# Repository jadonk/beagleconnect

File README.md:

# BeagleConnect
The purpose of BeagleConnect is to eliminate the need to write software to connect to a massive library of [sensors](https://en.wikipedia.org/wiki/Sensor), [actuators](https://en.wikipedia.org/wiki/Actuator) and [indicators](https://en.wikipedia.org/wiki/Indicator_(distance_amplifying_instrument)). These are the tools used to automate things in [mechatronics](https://en.wikipedia.org/wiki/Mechatronics) and [IoT](https://en.wikipedia.org/wiki/Internet_of_things).

BeagleConnect solves:
* The need to write software to add a large set of diverse devices to your system,
* The need to maintain the software with security updates,
* The need to rapidly prototype using off-the-shelf software and hardware without wiring,
* The need to connect to devices using long-range, low-power wireless, and
* The need to produce high-volume custom hardware cost-optimized for your requirements.

The minimally viable BeagleConnect development release:
* Supports at least 100 mikroBUS-based Click boards from Mikroelectronika,
* Works with BLE-enabled Linux computers at 2.4GHz,
* Works on long-range sub-GHz at 500m with data rates of 1kbps, and
* Comprises of low-cost BeagleBoard.org Linux SBC, a BeagleConnect gateway, and at least 10 BeagleConnect device nodes each supporting 2 add-on devices.

A wireless BeagleConnect board for adding a new device node is targeted to cost under US$10.

Future releases will be collaborated with the community, evolve dynamically, and contain additional functionality. The goal is to support over 500 add-on devices within the first year after the development release.

_Aside_: The term BeagleConnect refers to a particular board as well as a family of boards, a collection of Linux kernel drivers, microcontroller firmware, communication protocol, and system-level integration to automation software tools. More specific terms will be applied in the architecture details. The term is meant to represent the experience to be introduced to users through the initial BeagleConnect board.

## BeagleConnect wireless board prototype rev B

# What is new?
BeagleConnect solves IoT in a different and better way than any previous solution.

## The device interface software is already done
BeagleConnect uses the collaboratively developed Linux kernel to contain the intelligence required to speak to these devices (sensors, actuators, and indicators), rather than relying on writing code on a microcontroller specific to these devices. Some existing solutions rely on large libraries of microcontroller code, but the integration of communications, maintenance of the library with a limited set of developer resources and other constraints to be explained later make those other solutions less suitable for rapid prototyping than BeagleConnect.

Linux presents these devices abstractly in ways that are self-descriptive. Add an accelerometer to the system and you are automatically fed a stream of force values in standard units. Add a temperature sensor and you get it back in standard units again. Same for sensing magnetism, proximity, color, light, frequency, orientation, or multitudes of other inputs. Indicators, such as LEDs and displays, are similarly abstracted with a few other kernel subsystems and more advanced actuators with and without feedback control are in the process of being developed and standardized. In places where proper Linux kernel drivers exist, no new specialized code needs to be created for the devices.

*Bottom line*: For hundreds of devices, users won't have to write a single line of code to add them their systems. The automation code they do write can be extremely simple, done with graphical tools or in any language they want. Maintenance of the code is centralized in a small reusable set of microcontroller firmware and the Linux kernel, which is highly peer reviewed under a [highly-regarded governance model](https://wiki.p2pfoundation.net/Linux_-_Governance).

## On-going maintenance
Because there isn't code specific to any given network-of-devices configuration, we can all leverage the same software code base. This means that when someone fixes an issue in either BeagleConnect firmware or the Linux kernel, you benefit from the fixes. The source for BeagleConnect firmware is also submitted to the [Zephyr Project](https://www.zephyrproject.org/) upstream, further increasing the user base. Additionally, we will maintain stable branches of the software and provide mechanisms for updating firmware on BeagleConnect hardware. With a single, relatively small firmware load, the potential for bugs is kept low. With large user base, the potential for discovering and resolving bugs is high.

## Rapid prototyping without wiring
BeagleConnect utilizes the [mikroBUS standard](https://elinux.org/Mikrobus). The mikroBUS standard interface is flexible enough for almost any typical sensor or indicator with hundreds of devices available.

## Long-range, low-power wireless
BeagleConnect wireless hardware is built around a [TI CC1352](http://www.ti.com/product/CC1352R) with TODO benefits.

## Full customization possible
BeagleConnect utilizes [open source hardware](https://www.oshwa.org/definition/) and [open source software](https://en.wikipedia.org/wiki/Open-source_software), making it possible to optimize hardware and software implementations and sourcing to meet end-product requirements. BeagleConnect is meant to enable rapid-prototyping and not to necessarily satisfy any particular end-product's requirements, but with full considerations for go-to-market needs.

BeagleConnect is:
* Available for at least 10 years,
* Built with fully open source software with submissions to mainline Linux and Zephyr repositories to aide in support and porting,
* Built with fully open source and non-restrictive hardware design including schematic, bill-of-materials, layout, and manufacturing files (with only the BeagleBoard.org logo removed due to licensing restrictions of our brand),
* Built with parts where at least a compatible part is available from worldwide distributors in any quantity,
* Built with design and manufacturing partners able to help scale derivative designs,
* Based on a security model using public/private keypairs that can be replaced to secure your own network, and
* Fully FCC/CE certified.

# Usage and development

## BeagleConnect user experience

### Enable a Linux host with BeagleConnect

Log into a host system running Linux that is BeagleConnect enabled. Enable a Linux host with BeagleConnect by plugging a BeagleConnect board into it's USB port. You'll also want to have another BeagleConnect board with a sensor, actuator or indicator device on it.

TODO: Currently the host is shown to be a PocketBeagle with a cape, but should likely be a different SBC with a BeagleConnect board connected over USB.

TODO: Currently the device is shown to be a Sensortag, but should likely be shown as a BeagleConnect with a Click Board device on it and a battery.

### Connect host and device

Initiate a connection between the host and devices by pressing the discovery button(s).

### Device data shows up as files

New streams of self-describing data show up on the host system using native device drivers.

## Components
* Host-side: BeagleConnect board connects a CC1352 to a Beagle or other Linux host over USB to serial
   * Provides long-range, low-power wireless communications
* Device-side: BeagleConnect board with a CC1352 is powered by a battery (coin cell or JST connector) or USB connector
   * Provides 2 mikroBUS connectors for connecting any of hundreds of [Click Board](https://bbb.io/click) mikroBUS add-on devices
* Standard firmware on the host-side and target-side CC1352s transport the standard busses
   * Paired with a Linux kernel driver
   * Provides new Linux host controllers for SPI, I2C, UART, PWM, ADC, and GPIO with interrupts
* Two-step provisioning
   * Enter provisioning mode by pressing the button on the host-side BeagleConnect
   * Press the button on any powered device-side BeagleConnect to add it to the network
      * The device interfaces get exposed to the host via Greybus BRIDGED_PHY protocol
      * The I2C bus is probed for a an identifier EEPROM and appropriate device drivers are loaded on the host
      * Unsupported Click Boards connected are exposed via userspace drivers on the host for development

### What's different
* No microcontroller code development is required by users
* Userspace drivers make rapid prototyping really easy
* Kernel drivers makes the support code collaborative parts of the Linux kernel, rather than cut-and-paste

## Development platform
* Linux machine
* 2x [CC1352R Launchpad](http://www.ti.com/tool/launchxl-cc1352r1)
* [Click BoosterPack 2](https://www.mikroe.com/click-booster-pack-2)

# Technical approach

BeagleConnect uses Greybus and updated Click Boards with identifiers to eliminate the need to add manually configure devices added onto the Linux system.

## High-level
* For Linux nerds: Think of BeagleConnect as [6LoWPAN](https://en.wikipedia.org/wiki/6LoWPAN) over [802.15.4](https://en.wikipedia.org/wiki/IEEE_802.15.4)-based [Greybus](https://kernel-recipes.org/en/2015/talks/an-introduction-to-greybus/) (instead of Unipro as used by Project Ara), where every BeagleConnect board shows up as new SPI, I2C, UART, PWM, ADC, and GPIO controllers that can now be probed to load drivers for the sensors or whatever is connected to them. (Proof of concept of Greybus over TCP/IP: https://www.youtube.com/watch?v=7H50pv-4YXw)
* For MCU folks: Think of BeagleConnect as a [Firmata](https://github.com/firmata/protocol)-style firmware load that exposes the interfaces for remote access over a secured wireless network. However, instead of using host software that knows how to speak the Firmata protocol, the Linux kernel speaks the slightly similar Greybus protocol to the MCU and exposes the device generically to users using a Linux kernel driver. Further, the Greybus protocol is spoken over [6LoWPAN](https://en.wikipedia.org/wiki/6LoWPAN) on [802.15.4](https://en.wikipedia.org/wiki/IEEE_802.15.4).

## Software architecture
* 802.15.4 provides the 

## TODO items
* Linux kernel driver
* Provisioning
   * Kconfig and what-not for adding a new BeagleDust to the network
   * Kconfig and what-not for configuring Clicks connected to BeagleDust
* Firmware for host CC13x
* Firmware for device CC13x
* Click Board drivers and device tree formatted metadata for 100 or so Click Boards
* Click Board plug-ins for node-red for the same 100 or so Click Boards
* BeagleDust System Reference Manual and FAQs

## Associated pre-work
* Click Board support for Node-RED can be executed with native connections on PocketBeagle+TechLab and BeagleBone Black with mikroBUS Cape
   * Device tree fragments and driver updates can be provided via https://bbb.io/click
* The Kconfig style provisioning can be implemented for those solutions, which will require a reboot. We need to centralize edits to /boot/uEnv.txt to be programmatic. As I think through this, I don't think BeagleConnect is impacted, because the Greybus-style discovery along with Click EEPROMS will eliminate any need to edit /boot/uEnv.txt.

## User experience concerns
* Make sure no reboots are required
* Plugging BeagleConnect into host should trigger host configuration
* Click EEPROMs should trigger loading whatever drivers are needed and provisioning should load any new drivers
* Userspace (spidev, etc.) drivers should unload cleanly when 2nd phase provisioning is completed

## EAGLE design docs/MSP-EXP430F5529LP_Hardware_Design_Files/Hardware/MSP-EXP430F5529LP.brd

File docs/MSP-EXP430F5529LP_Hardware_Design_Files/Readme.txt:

MSP-EXP430F5529LP Hardware Design Files v1.05.00
Texas Instruments, Inc.

********************************************************************************
Welcome to the MSP-EXP430F5529LP LaunchPad!
********************************************************************************

In this package, you will find hardware design files that can help you quickly
get started on developing your own project.

Available in the 'Hardware' folder are the complete board schematic and layout,
bill of material and Gerber files.

You can also find various web links in the 'Documentation' folder pointing to
the Tool Page, Quick Start Guide, User's Guide and MSP430 USB Developers Package.

For more resources, be sure to visit http://www.ti.com/tool/MSP-EXP430F5529LP
Also checkout the Wiki page at http://processors.wiki.ti.com/index.php/MSP430F5529_LaunchPad

********************************************************************************
Revision History
********************************************************************************
Ver 1.05.00 - June 22nd, 2015
- Added MacOSX + Linux support for MSP430Flasher

Ver 1.04.00 - March 24th, 2015
- Updated driverlib and USB stack in software examples

Ver 1.03.00 - September 26th, 2014
- Updated Hardware files to Revision 1.6

Ver 1.02.00 - June 23rd, 2014
- Updated release packages to distribute hardware and software files separately

Ver 1.01.00 - Jan 2nd, 2014
- Updated Hardware files to Revision 1.5

Ver 1.00.01 - October 09th, 2013
- Added Code Size limited project for emulStorageKeyboard
- Added new folder to include emulation tool driver and simpleUsbBackChannel driver

Ver 1.00.00 - August 27th, 2013
- Initial Release

********************************************************************************
Project File Listing
********************************************************************************
|--Documentation              : Folder containing links to more resources
|--Hardware                   : Folder containing board design files, bill of
                                material and gerber files
|--Readme.txt                 : This file

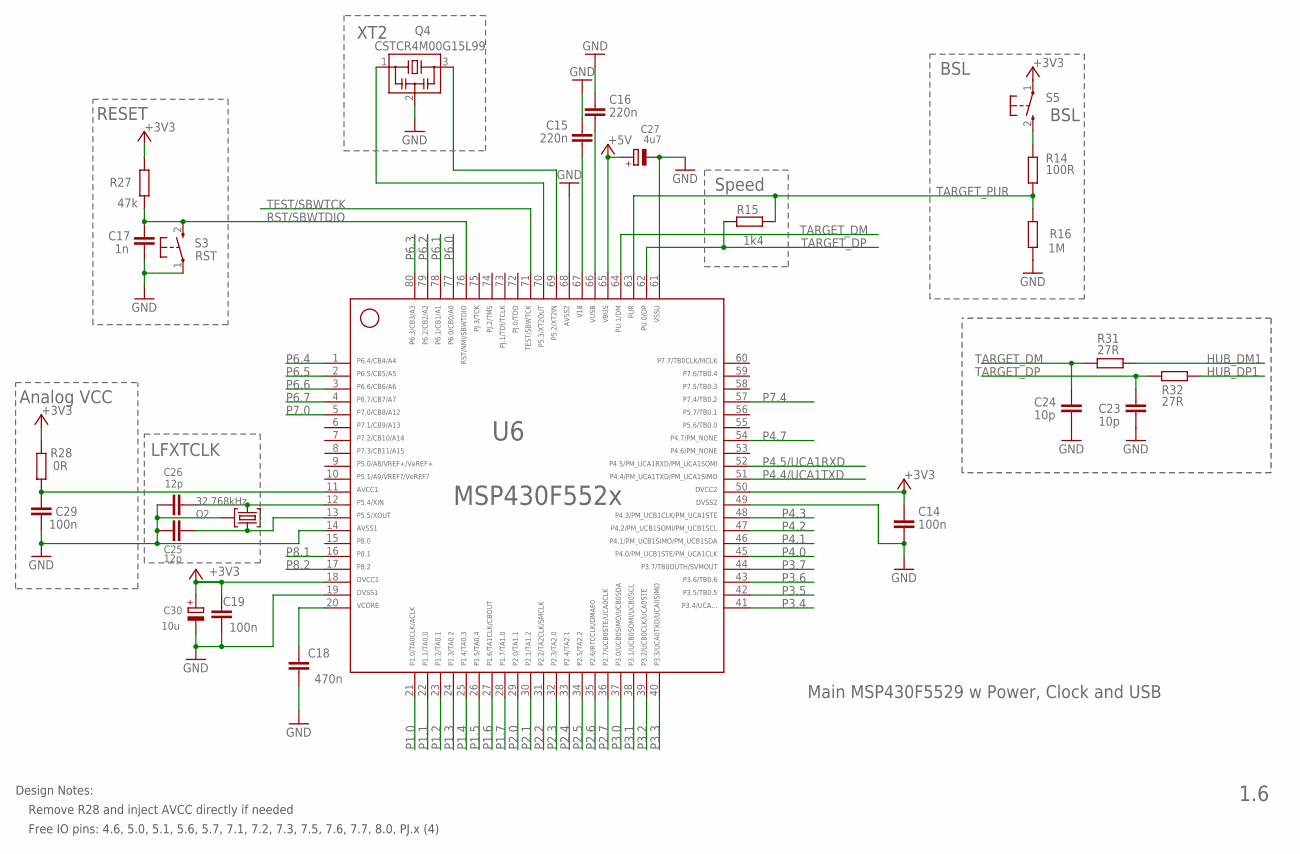
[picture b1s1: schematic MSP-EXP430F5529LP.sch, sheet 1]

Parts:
C14, C19, C29: 100n; 0402
C15, C16: 220n; 0402
C17: 1n; 0402
C18: 470n; 0402
C23, C24: 10p; 0402
C25, C26: 12p; 0402
C27: 4u7; A/3216-18R
C30: 10u; A/3216-18R
Q2: 32.768kHz; MS3V-T1R
Q4: CSTCR4M00G15L99; MURATA-FILTER_CSTCR
R14: 100R; 0402
R15: 1k4; 0402
R16: 1M; 0402
R27: 47k; 0402
R28: 0R; 0402
R31, R32: 27R; 0402
S3: RST; PBTH
S5: BSL; PBTH
U6: MSP430F5529IPNR; PN80

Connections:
+3V3: C14.1, C19.2, C30.+, R27.2, R28.2, S5.1, U6.18, U6.50; also elsewhere on the board
+5V: C27.+, U6.65; also elsewhere on the board
AVCC: C29.1, R28.1, U6.11
GND: C14.2, C15.2, C16.2, C17.2, C18.1, C19.1, C23.2, C24.2, C25.1, C26.1, C27.-, C29.2, C30.-, Q2.P3 (GND), Q4.2, R16.1, S3.1, U6.14, U6.19, U6.49, U6.61, U6.68; also elsewhere on the board
HUB_DM1: R31.1; also elsewhere on the board
HUB_DP1: R32.1; also elsewhere on the board
unnamed: R14.1, S5.2 (S)
P1.0: U6.21; also elsewhere on the board
P1.1: U6.22; also elsewhere on the board
P1.2: U6.23; also elsewhere on the board
P1.3: U6.24; also elsewhere on the board
P1.4: U6.25; also elsewhere on the board
P1.5: U6.26; also elsewhere on the board
P1.6: U6.27; also elsewhere on the board
P1.7: U6.28; also elsewhere on the board
P2.0: U6.29; also elsewhere on the board
P2.1: U6.30; also elsewhere on the board
P2.2: U6.31; also elsewhere on the board
P2.3: U6.32; also elsewhere on the board
P2.4: U6.33; also elsewhere on the board
P2.5: U6.34; also elsewhere on the board
P2.6: U6.35; also elsewhere on the board
P2.7: U6.36; also elsewhere on the board
P3.0: U6.37; also elsewhere on the board
P3.1: U6.38; also elsewhere on the board
P3.2: U6.39; also elsewhere on the board
P3.3: U6.40; also elsewhere on the board
P3.4: U6.41; also elsewhere on the board
P3.5: U6.42; also elsewhere on the board
P3.6: U6.43; also elsewhere on the board
P3.7: U6.44; also elsewhere on the board
P4.0: U6.45; also elsewhere on the board
P4.1: U6.46; also elsewhere on the board
P4.2: U6.47; also elsewhere on the board
P4.3: U6.48; also elsewhere on the board
P4.4/UCA1TXD: U6.51; also elsewhere on the board
P4.5/UCA1RXD: U6.52; also elsewhere on the board
P4.7: U6.54; also elsewhere on the board
P5.2/XT2IN: Q4.3, U6.69
P5.3/XT2OUT: Q4.1, U6.70
P5.4/XIN: C26.2, Q2.P2 (2), U6.12
P5.5/XOUT: C25.2, Q2.P1 (1), U6.13
P6.0: U6.77; also elsewhere on the board
P6.1: U6.78; also elsewhere on the board
P6.2: U6.79; also elsewhere on the board
P6.3: U6.80; also elsewhere on the board
P6.4: U6.1; also elsewhere on the board
P6.5: U6.2; also elsewhere on the board
P6.6: U6.3; also elsewhere on the board
P6.7: U6.4; also elsewhere on the board
P7.0: U6.5; also elsewhere on the board
P7.4: U6.57; also elsewhere on the board
P8.1: U6.16; also elsewhere on the board
P8.2: U6.17; also elsewhere on the board
RST/SBWTDIO: C17.1, R27.1, S3.2 (S), U6.76; also elsewhere on the board
TARGET_DM: C24.1, R31.2, U6.64
TARGET_DP: C23.1, R15.2, R32.2, U6.62
TARGET_PUR: R14.2, R15.1, R16.2, U6.63
TARGET_VUSB: C16.1, U6.66
TEST/SBWTCK: U6.71; also elsewhere on the board
V18: C15.1, U6.67
VCORE: C18.2, U6.20

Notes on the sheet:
RESET
LFXTCLK
XT2
Main MSP430F5529 w Power, Clock and USB
1.6
BSL
Speed
Analog VCC
Remove R28 and inject AVCC directly if needed
Design Notes:
Free IO pins: 4.6, 5.0, 5.1, 5.6, 5.7, 7.1, 7.2, 7.3, 7.5, 7.6, 7.7, 8.0, PJ.x (4)

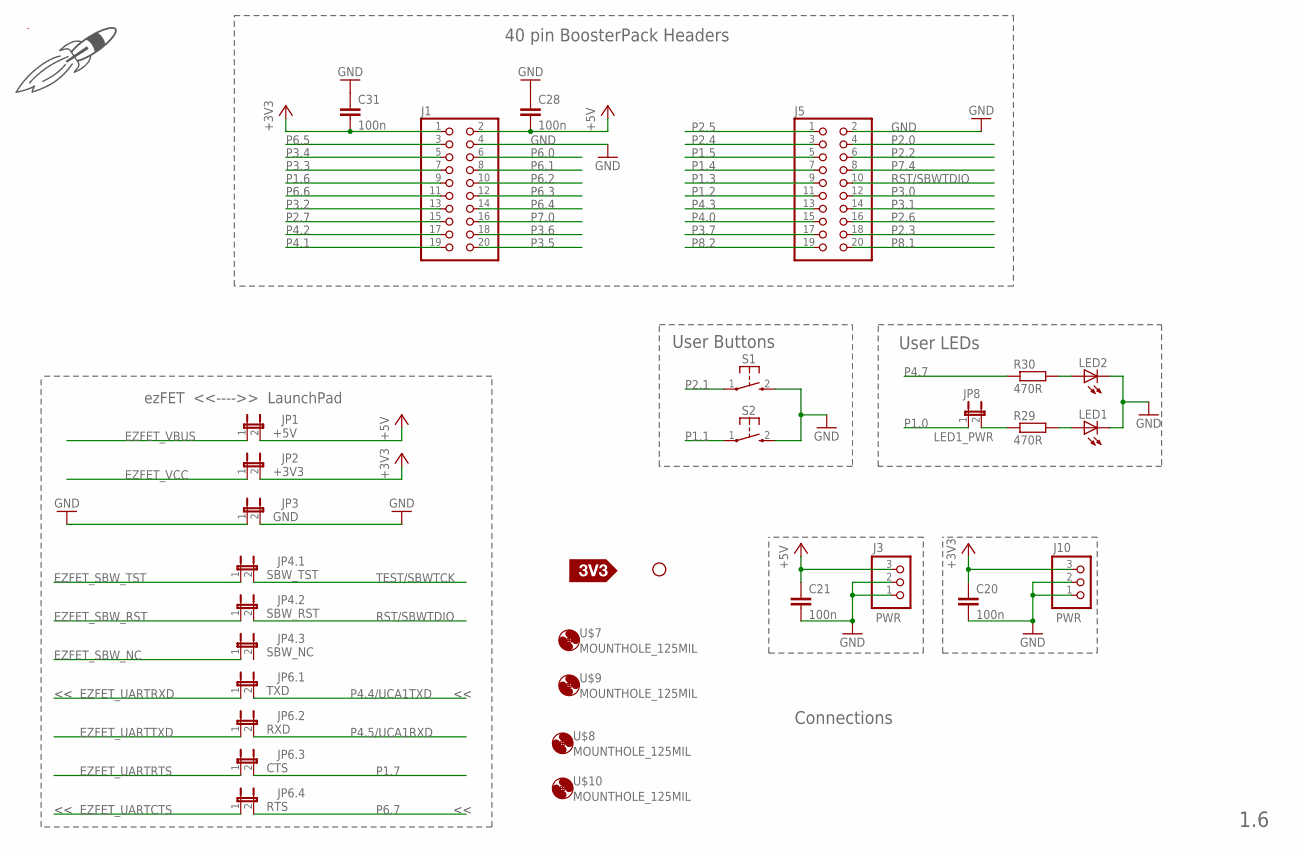
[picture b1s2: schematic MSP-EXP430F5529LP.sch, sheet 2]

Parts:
C20, C21, C28, C31: 100n; 0402
DRAW1: LOGO-ROCKET-20X13MM-SCH-S; LOGO-ROCKET-10X7MM-BRD
J1, J5: PINHD-2X10; 2X10
J3, J10: PWR; 1X03
JP1: +5V; JP1M
JP2: +3V3; JP1M
JP3: GND; JP1M
JP4.1: SBW_TST; JP1M
JP4.2: SBW_RST; JP1M
JP4.3: SBW_NC; JP1M
JP6.1: TXD; JP1M
JP6.2: RXD; JP1M
JP6.3: CTS; JP1M
JP6.4: RTS; JP1M
JP8: LED1_PWR; JP1
LED1, LED2: LEDCHIPLED_0603; CHIPLED_0603
R29, R30: 470R; 0402
S1, S2: PB; PBTH
U$4: MS_TM
U$6: SILK_3V3_TAG
U$7, U$8, U$9, U$10: MOUNTHOLE_125MIL
U$11: 5529LP_REARSILK_REV1_6

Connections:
+3V3: C20.1, C31.2, J1.1, J10.3, JP2.2; also elsewhere on the board
+5V: C21.1, C28.2, J1.2, J3.3, JP1.2; also elsewhere on the board
EZFET_SBW_NC: JP4.3.1; also elsewhere on the board
EZFET_SBW_RST: JP4.2.1; also elsewhere on the board
EZFET_SBW_TST: JP4.1.1; also elsewhere on the board
EZFET_UARTCTS: JP6.4.1; also elsewhere on the board
EZFET_UARTRTS: JP6.3.1; also elsewhere on the board
EZFET_UARTRXD: JP6.1.1; also elsewhere on the board
EZFET_UARTTXD: JP6.2.1; also elsewhere on the board
EZFET_VBUS: JP1.1; also elsewhere on the board
EZFET_VCC: JP2.1; also elsewhere on the board
GND: C20.2, C21.2, C28.1, C31.1, J1.4, J3.1, J3.2, J5.2, J10.1, J10.2, JP3.1, JP3.2, LED1.C, LED2.C, S1.2 (S), S2.2 (S); also elsewhere on the board
unnamed: JP8.2, R29.1
unnamed: LED1.A, R29.2
unnamed: LED2.A, R30.2
P1.0: JP8.1; also elsewhere on the board
P1.1: S2.1; also elsewhere on the board
P1.2: J5.11; also elsewhere on the board
P1.3: J5.9; also elsewhere on the board
P1.4: J5.7; also elsewhere on the board
P1.5: J5.5; also elsewhere on the board
P1.6: J1.9; also elsewhere on the board
P1.7: JP6.3.2; also elsewhere on the board
P2.0: J5.4; also elsewhere on the board
P2.1: S1.1; also elsewhere on the board
P2.2: J5.6; also elsewhere on the board
P2.3: J5.18; also elsewhere on the board
P2.4: J5.3; also elsewhere on the board
P2.5: J5.1; also elsewhere on the board
P2.6: J5.16; also elsewhere on the board
P2.7: J1.15; also elsewhere on the board
P3.0: J5.12; also elsewhere on the board
P3.1: J5.14; also elsewhere on the board
P3.2: J1.13; also elsewhere on the board
P3.3: J1.7; also elsewhere on the board
P3.4: J1.5; also elsewhere on the board
P3.5: J1.20; also elsewhere on the board
P3.6: J1.18; also elsewhere on the board
P3.7: J5.17; also elsewhere on the board
P4.0: J5.15; also elsewhere on the board
P4.1: J1.19; also elsewhere on the board
P4.2: J1.17; also elsewhere on the board
P4.3: J5.13; also elsewhere on the board
P4.4/UCA1TXD: JP6.1.2; also elsewhere on the board
P4.5/UCA1RXD: JP6.2.2; also elsewhere on the board
P4.7: R30.1; also elsewhere on the board
P6.0: J1.6; also elsewhere on the board
P6.1: J1.8; also elsewhere on the board
P6.2: J1.10; also elsewhere on the board
P6.3: J1.12; also elsewhere on the board
P6.4: J1.14; also elsewhere on the board
P6.5: J1.3; also elsewhere on the board
P6.6: J1.11; also elsewhere on the board
P6.7: JP6.4.2; also elsewhere on the board
P7.0: J1.16; also elsewhere on the board
P7.4: J5.8; also elsewhere on the board
P8.1: J5.20; also elsewhere on the board
P8.2: J5.19; also elsewhere on the board
RST/SBWTDIO: J5.10, JP4.2.2; also elsewhere on the board
TEST/SBWTCK: JP4.1.2; also elsewhere on the board

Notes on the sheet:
40 pin BoosterPack Headers
Connections
1.6
User LEDs
User Buttons
ezFET <<---->> LaunchPad

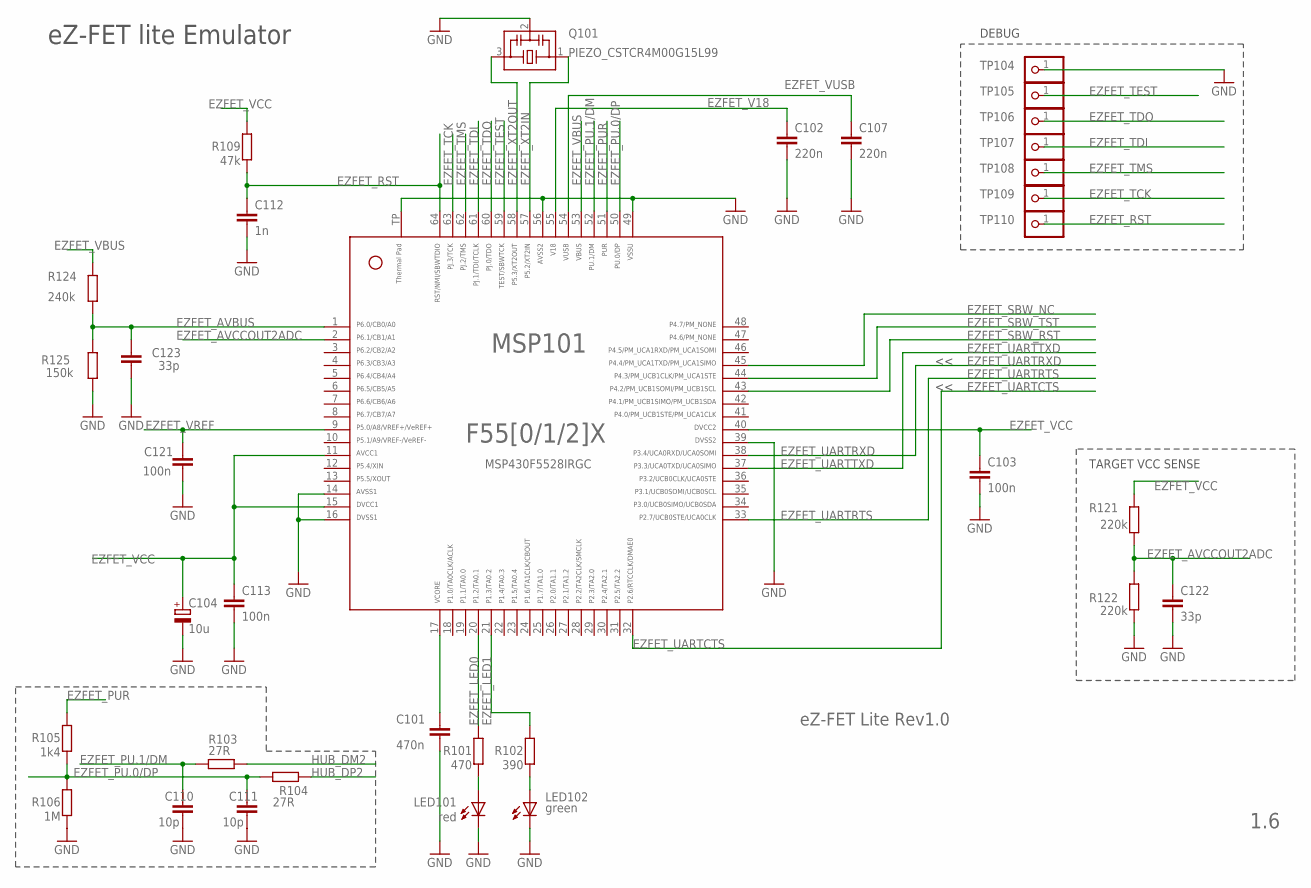
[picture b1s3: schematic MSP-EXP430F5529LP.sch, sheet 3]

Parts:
C101: 470n; 0402
C102, C107: 220n; 0402
C103, C113, C121: 100n; 0402
C104: 10u; A/3216-18R
C110, C111: 10p; 0402
C112: 1n; 0402
C122, C123: 33p; 0402
LED101: red; CHIP-LED0603
LED102: green; CHIP-LED0603
MSP101: MSP430F5528IRGC; RGC64
Q101: PIEZO_CSTCR4M00G15L99; MURATA-FILTER_CSTCR
R101: 470; 0402
R102: 390; 0402
R103, R104: 27R; 0402
R105: 1k4; 0402
R106: 1M; 0402
R109: 47k; 0402
R121, R122: 220k; 0402
R124: 240k; 0402
R125: 150k; 0402
TP104, TP105, TP106, TP107, TP108, TP109, TP110: TEST_PIN2; 1X01

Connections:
EZFET_AVBUS: C123.2, MSP101.1, R124.2, R125.1
EZFET_AVCCOUT2ADC: C122.2, MSP101.2, R121.2, R122.1
EZFET_LED0: MSP101.20, R101.2
EZFET_LED1: MSP101.21, R102.2
EZFET_PU.0/DP: C111.1, MSP101.50, R104.2, R105.1, R106.2
EZFET_PU.1/DM: C110.1, MSP101.52, R103.2
EZFET_PUR: MSP101.51, R105.2
EZFET_RST: C112.1, MSP101.64, R109.1, TP110.1
EZFET_SBW_NC: MSP101.45; also elsewhere on the board
EZFET_SBW_RST: MSP101.43; also elsewhere on the board
EZFET_SBW_TST: MSP101.44; also elsewhere on the board
EZFET_TCK: MSP101.63, TP109.1
EZFET_TDI: MSP101.61, TP107.1
EZFET_TDO: MSP101.60, TP106.1
EZFET_TEST: MSP101.59, TP105.1
EZFET_TMS: MSP101.62, TP108.1
EZFET_UARTCTS: MSP101.32; also elsewhere on the board
EZFET_UARTRTS: MSP101.33; also elsewhere on the board
EZFET_UARTRXD: MSP101.38; also elsewhere on the board
EZFET_UARTTXD: MSP101.37; also elsewhere on the board
EZFET_V18: C102.1, MSP101.55
EZFET_VBUS: MSP101.53, R124.1; also elsewhere on the board
EZFET_VCC: C103.1, C104.+, C113.1, MSP101.11, MSP101.15, MSP101.40, R109.2, R121.1; also elsewhere on the board
EZFET_VREF: C121.1, MSP101.9
EZFET_VUSB: C107.1, MSP101.54
EZFET_XT2IN: MSP101.57, Q101.1
EZFET_XT2OUT: MSP101.58, Q101.3
GND: C101.2, C102.2, C103.2, C104.-, C107.2, C110.2, C111.2, C112.2, C113.2, C121.2, C122.1, C123.1, LED101.C, LED102.C, MSP101.14, MSP101.16, MSP101.39, MSP101.49, MSP101.56, MSP101.TP, Q101.2, R106.1, R122.2, R125.2, TP104.1; also elsewhere on the board
HUB_DM2: R103.1; also elsewhere on the board
HUB_DP2: R104.1; also elsewhere on the board
unnamed: LED101.A, R101.1
unnamed: LED102.A, R102.1
unnamed: C101.1, MSP101.17

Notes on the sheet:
eZ-FET lite Emulator
MSP430F5528IRGC
TARGET VCC SENSE
eZ-FET Lite Rev1.0
1.6
DEBUG

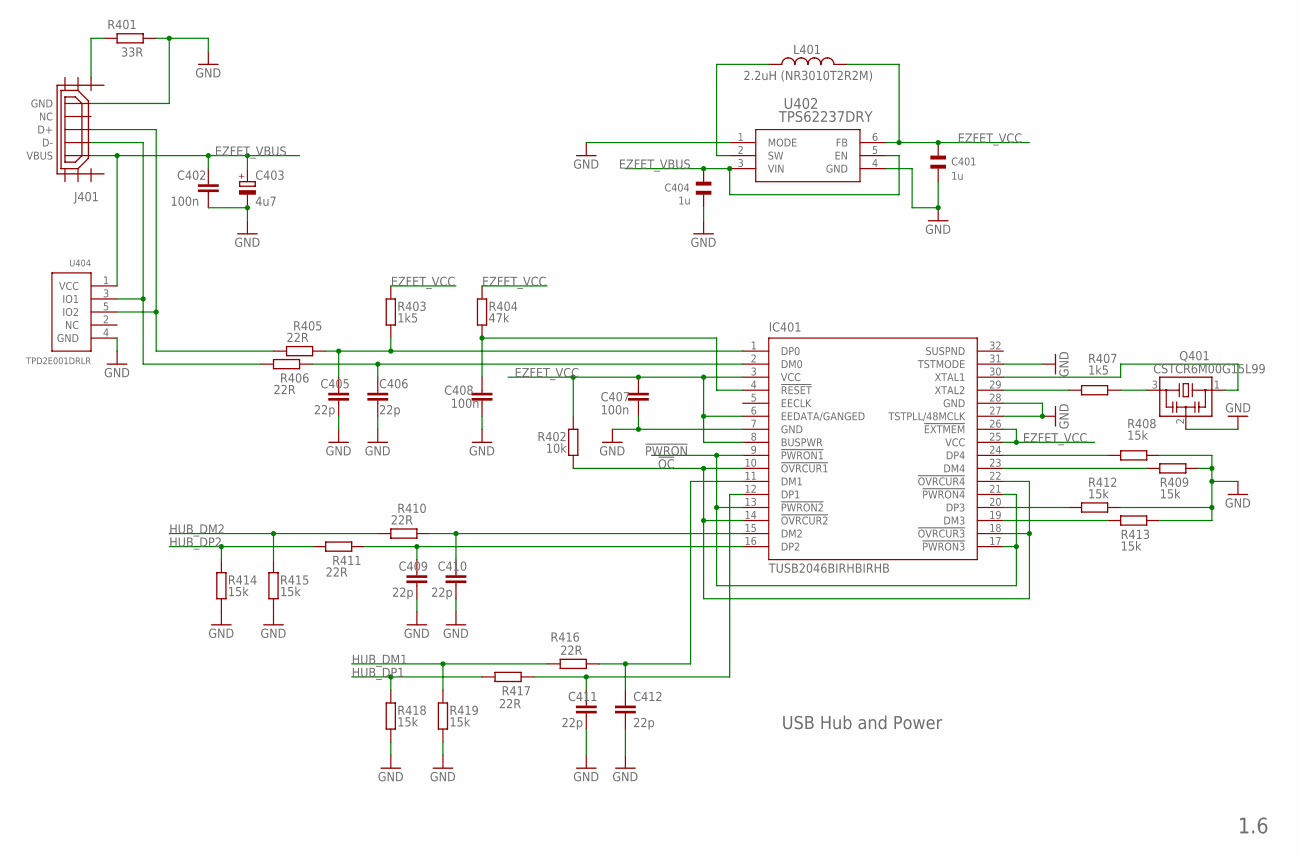
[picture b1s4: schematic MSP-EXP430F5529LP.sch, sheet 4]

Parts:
C401, C404: 1u; CSMD0805
C402, C407, C408: 100n; 0402
C403: 4u7; A/3216-18R
C405, C406, C409, C410, C411, C412: 22p; 0402
IC401: TUSB2046BIRHBIRHB; RHB_S-PQFP-N32
J401: USB_MICRO_FLIPPED; HIROSE-ZX62R-B-5P
L401: 2.2uH (NR3010T2R2M); L-NR3010
Q401: CSTCR6M00G15L99; MURATA-FILTER_CSTCR
R401: 33R; 0402
R402: 10k; 0402
R403, R407: 1k5; 0402
R404: 47k; 0402
R405, R406, R410, R411, R416, R417: 22R; 0402
R408, R409, R412, R413, R414, R415, R418, R419: 15k; 0402
U402: TPS62237DRY; DRY6
U404: TPD2E001DRLR; TPD2E001-DRL

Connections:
!OC: IC401.10 (!OVRCUR1), IC401.14 (!OVRCUR2), IC401.18 (!OVRCUR3), IC401.22 (!OVRCUR4), R402.2
!PWRON: IC401.9 (!PWRON1), IC401.13 (!PWRON2), IC401.17 (!PWRON3), IC401.21 (!PWRON4)
EZFET_VBUS: C402.1, C403.+, C404.2, J401.VBUS, U402.3 (VIN), U402.5 (EN), U404.1 (VCC); also elsewhere on the board
EZFET_VCC: C401.2, C407.1, IC401.3 (VCC), IC401.6 (EEDATA/GANGED), IC401.8 (BUSPWR), IC401.25 (VCC), IC401.26 (!EXTMEM), L401.P$2 (2), R402.1, R403.1, R404.1, U402.6 (FB); also elsewhere on the board
GND: C401.1, C402.2, C403.-, C404.1, C405.2, C406.2, C407.2, C408.2, C409.2, C410.2, C411.2, C412.2, IC401.7 (GND), IC401.27 (TSTPLL/48MCLK), IC401.28 (GND), IC401.31 (TSTMODE), J401.GND, Q401.2, R401.2, R408.1, R409.1, R412.1, R413.1, R414.2, R415.2, R418.2, R419.2, U402.1 (MODE), U402.4 (GND), U404.4 (GND); also elsewhere on the board
HUB_DM1: R416.2, R419.1; also elsewhere on the board
HUB_DM2: R410.2, R415.1; also elsewhere on the board
HUB_DP1: R417.2, R418.1; also elsewhere on the board
HUB_DP2: R411.2, R414.1; also elsewhere on the board
unnamed: C410.1, IC401.15 (DM2), R410.1
unnamed: C405.1, IC401.1 (DP0), R403.2, R405.1
unnamed: IC401.30 (XTAL1), Q401.1
unnamed: J401.SHIELD1, R401.1
unnamed: C406.1, IC401.2 (DM0), R406.1
unnamed: J401.D+, R405.2, U404.5 (IO2)
unnamed: J401.D-, R406.2, U404.3 (IO1)
unnamed: L401.P$1 (1), U402.2 (SW)
unnamed: IC401.29 (XTAL2), R407.2
unnamed: C412.1, IC401.11 (DM1), R416.1
unnamed: C411.1, IC401.12 (DP1), R417.1
unnamed: C409.1, IC401.16 (DP2), R411.1
unnamed: C408.1, IC401.4 (!RESET), R404.2
unnamed: IC401.20 (DP3), R412.2
unnamed: IC401.24 (DP4), R408.2
unnamed: IC401.23 (DM4), R409.2
unnamed: IC401.19 (DM3), R413.2
unnamed: Q401.3, R407.1

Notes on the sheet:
USB Hub and Power
1.6

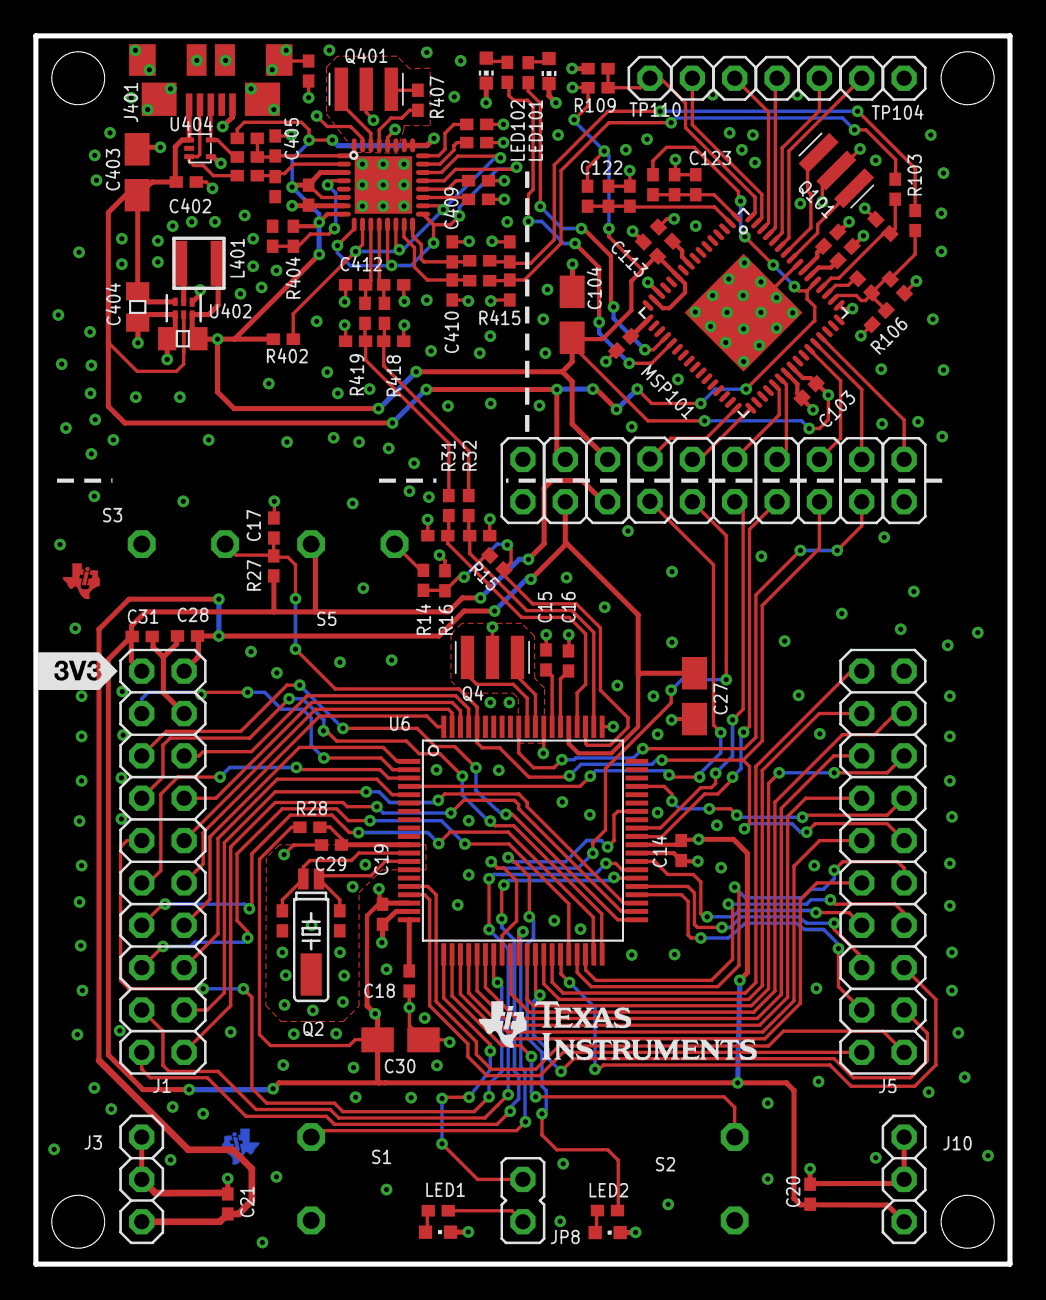
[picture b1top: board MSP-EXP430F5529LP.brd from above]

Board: 2 copper layers, 58.4 x 73.7 mm, 133 parts (1 on the bottom side), 117 nets.

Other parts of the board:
DRAW2: LOGO-ROCKET-10X7MM-BRD
U$1: LOGO16_TPLACE
U$2, U$5: TILOGO_SMALL

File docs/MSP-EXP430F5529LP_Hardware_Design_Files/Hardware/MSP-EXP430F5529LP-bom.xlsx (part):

BOM for MSP-EXP430F5529LP
Do not populate (Dnp) part if Quantity equals zero
Use exact PartNumber and Manufacturer if this data is provided
Feedback from ContractManufacturer (CM) needed where supplier equals CM
ezFET or EXP? | Qty | Reference | Manufacturer | Description | Part Number | PCB DECAL/Package | Value | Supplier1 | Digikey Number | Rev1.4 to Rev 1.5 Change
Box | 1 |  | CM | MicroUSB cable. Lierda to suggest part | tbd | Box | Micro USB cable | CM | to be provided by CM
ezFET | 1 | C101 | Standard | CAP CER 0.47UF 16V 10% X5R 0402,Digikey 445-4976-1-ND |  | C0402 | 470n | Digikey | 445-4976-1-ND
ezFET | 1 | C102 | Standard | CAP CER 0.22UF 16V 10% X5R 0402,Digikey 445-4972-1-ND |  | C0402 | 220n | Digikey | 445-4972-1-ND
ezFET | 1 | C103 | Standard | CAP CER 0.1UF 10V 20% X5R 0402,Digikey 445-4984-1-ND |  | C0402 | 100n | Digikey | 445-4984-1-ND
ezFET | 1 | C104 | Standard | CAP TANT 10UF 10V 20% 1206,Digikey 493-2351-1-ND |  | TANT_3216 | 10u | Digikey | 493-2351-1-ND
ezFET | 1 | C107 | Standard | CAP CER 0.22UF 16V 10% X5R 0402,Digikey 445-4972-1-ND |  | C0402 | 220n | Digikey | 445-4972-1-ND
ezFET | 1 | C110 | Standard | CAP CER 10PF 50V NP0 0402,Digikey 445-1235-1-ND |  | C0402 | 10p | Digikey | 445-1235-1-ND
ezFET | 1 | C111 | Standard | CAP CER 10PF 50V NP0 0402,Digikey 445-1235-1-ND |  | C0402 | 10p | Digikey | 445-1235-1-ND
ezFET | 1 | C112 | Standard | CAP CER 1000PF 50V 10% X7R 0402,Digikey 445-1256-1-ND |  | C0402 | 1n | Digikey | 445-1256-1-ND
ezFET | 1 | C113 | Standard | CAP CER 0.1UF 10V 20% X5R 0402,Digikey 445-4984-1-ND |  | C0402 | 100n | Digikey | 445-4984-1-ND
ezFET | 1 | C121 | Standard | CAP CER 0.1UF 10V 20% X5R 0402,Digikey 445-4984-1-ND |  | C0402 | 100n | Digikey | 445-4984-1-ND
ezFET | 1 | C122 | Standard | CAP CER 33PF 50V 5% NP0 0402,Digikey 445-1241-1-ND |  | C0402 | 33p | Digikey | 445-1241-1-ND
ezFET | 1 | C123 | Standard | CAP CER 33PF 50V 5% NP0 0402,Digikey 445-1241-1-ND |  | C0402 | 33p | Digikey | 445-1241-1-ND
LP | 1 | C14 | Standard | CAP CER 0.1UF 10V 20% X5R 0402,Digikey 445-4984-1-ND |  | C0402 | 100n | Digikey | 445-4984-1-ND
LP | 1 | C15 | Standard | CAP CER 0.22UF 16V 10% X5R 0402,Digikey 445-4972-1-ND |  | C0402 | 220n | Digikey | 445-4972-1-ND
LP | 1 | C16 | Standard | CAP CER 0.22UF 16V 10% X5R 0402,Digikey 445-4972-1-ND |  | C0402 | 220n | Digikey | 445-4972-1-ND
LP | 1 | C17 | Standard | CAP CER 1000PF 50V 10% X7R 0402,Digikey 445-1256-1-ND |  | C0402 | 1n | Digikey | 445-1256-1-ND
LP | 1 | C18 | Standard | CAP CER 0.47UF 16V 10% X5R 0402,Digikey 445-4976-1-ND |  | C0402 | 470n | Digikey | 445-4976-1-ND
LP | 1 | C19 | Standard | CAP CER 0.1UF 10V 20% X5R 0402,Digikey 445-4984-1-ND |  | C0402 | 100n | Digikey | 445-4984-1-ND
LP | 1 | C20 | Standard | CAP CER 0.1UF 10V 20% X5R 0402,Digikey 445-4984-1-ND |  | C0402 | 100n | Digikey | 445-4984-1-ND
LP | 1 | C21 | Standard | CAP CER 0.1UF 10V 20% X5R 0402,Digikey 445-4984-1-ND |  | C0402 | 100n | Digikey | 445-4984-1-ND
LP | 1 | C23 | Standard | CAP CER 10PF 50V 5%NP0 0402,Digikey 445-1235-1-ND |  | C0402 | 10p | Digikey | 445-1235-1-ND
LP | 1 | C24 | Standard | CAP CER 10PF 50V 5% NP0 0402,Digikey 445-1235-1-ND |  | C0402 | 10p | Digikey | 445-1235-1-ND
LP | 1 | C25 | Standard | CAP CER 12PF 50V 5% NP0 0402,Digikey 445-1236-1-ND |  | C0402 | 12p | Digikey | 445-1236-1-ND
LP | 1 | C26 | Standard | CAP CER 12PF 50V 5% NP0 0402,Digikey 445-1236-1-ND |  | C0402 | 12p | Digikey | 445-1236-1-ND
LP | 1 | C27 | Standard | CAP TANT 4.7UF 10V 10% 1206,Digikey 493-4142-1-ND |  | A/3216-18R | 4u7 | Digikey | 493-4142-1-ND
LP | 1 | C28 | Standard | CAP CER 0.1UF 10V 20% X5R 0402,Digikey 445-4984-1-ND |  | C0402 | 100n | Digikey | 445-4984-1-ND
LP | 1 | C29 | Standard | CAP CER 0.1UF 10V 20% X5R 0402,Digikey 445-4984-1-ND |  | C0402 | 100n | Digikey | 445-4984-1-ND
LP | 1 | C30 | Standard | CAP TANT 10UF 10V 20% 1206,Digikey 493-2351-1-ND |  | TANT_3216 | 10u | Digikey | 493-2351-1-ND
LP | 1 | C31 | Standard | CAP CER 0.1UF 10V 20% X5R 0402,Digikey 445-4984-1-ND |  | C0402 | 100n | Digikey | 445-4984-1-ND
Hub | 1 | C401 | Standard | CAP CER 1UF 10V 10% X7R 0805,Digikey 587-1284-2-ND |  | CSMD0805 | 1u | Digikey | 587-1284-2-ND
Hub | 1 | C402 | Standard | CAP CER 0.1UF 10V 20% X5R 0402,Digikey 445-4984-1-ND |  | C0402 | 100n | Digikey | 445-4984-1-ND
Hub | 1 | C403 | Standard | CAP TANT 4.7UF 10V 10% 1206,Digikey 493-4142-1-ND |  | A/3216-18R | 4u7 | Digikey | 493-4142-1-ND
Hub | 1 | C404 | Standard | CAP CER 1UF 10V 10% X7R 0805,Digikey 587-1284-2-ND |  | CSMD0805 | 1u | Digikey | 587-1284-2-ND
Hub | 1 | C405 | Standard | CAP CER 22PF 50V 5% NP0 0402,Digikey 445-1239-1-ND |  | C0402 | 22p | Digikey | 445-1239-1-ND
Hub | 1 | C406 | Standard | CAP CER 22PF 50V 5% NP0 0402,Digikey 445-1239-1-ND |  | C0402 | 22p | Digikey | 445-1239-1-ND
Hub | 1 | C407 | Standard | CAP CER 0.1UF 10V 20% X5R 0402,Digikey 445-4984-1-ND |  | C0402 | 100n | Digikey | 445-4984-1-ND
Hub | 1 | C408 | Standard | CAP CER 0.1UF 10V 20% X5R 0402,Digikey 445-4984-1-ND |  | C0402 | 100n | Digikey | 445-4984-1-ND
Hub | 1 | C409 | Standard | CAP CER 22PF 50V 5% NP0 0402,Digikey 445-1239-1-ND |  | C0402 | 22p | Digikey | 445-1239-1-ND
Hub | 1 | C410 | Standard | CAP CER 22PF 50V 5% NP0 0402,Digikey 445-1239-1-ND |  | C0402 | 22p | Digikey | 445-1239-1-ND
Hub | 1 | C411 | Standard | CAP CER 22PF 50V 5% NP0 0402,Digikey 445-1239-1-ND |  | C0402 | 22p | Digikey | 445-1239-1-ND
Hub | 1 | C412 | Standard | CAP CER 22PF 50V 5% NP0 0402,Digikey 445-1239-1-ND |  | C0402 | 22p | Digikey | 445-1239-1-ND
Hub | 1 | IC401 | TI | IC 4-PORT HUB FOR USB 32-QFN,Digikey 296-21926-1-ND | TUSB2046BIRHBR | RHB_S-PQFP-N32 | TUSB2046BIRHBIRHB | Digikey | 296-21926-1-ND
LP | 1 | J1 | CM | CONN HEADER 20POS .100" DUAL, FEMALE with long male leads | CNT-F254-2*10-GS-850-9 | 2X10 |  | CM | to be provided by CM | Updated part # for stronger male leads
LP | 1 | J10 | Standard | CONN HEADER 3POS .100" SNGL TIN,Digikey SAM1075-03-ND |  | 1X03 | PWR | Digikey | SAM1075-03-ND
LP | 1 | J3 | Standard | CONN HEADER 3POS .100" SNGL TIN,Digikey SAM1075-03-ND |  | 1X03 | PWR | Digikey | SAM1075-03-ND
Hub | 1 | J401 | Standard | CONN RCPT MICRO USB B SMD R/A, Digikey H11574CT-ND |  | CONN_USB-MICRO-B-SMT_R | ZX62R-B-5P | Digikey | H11574CT-ND
LP | 1 | J5 | CM | CONN HEADER 20POS .100" DUAL, FEMALE with long male leads | CNT-F254-2*10-GS-850-9 | 2X10 |  | CM | to be provided by CM | Updated part # for stronger male leads
LP | 1 | JP1 | Standard | CONN HEADER 2POS .100" SNGL TIN,Digikey SAM1075-02-ND |  | JP1M | +5V | Digikey | SAM1075-02-ND
LP | 1 | JP2 | Standard | CONN HEADER 2POS .100" SNGL TIN,Digikey SAM1075-02-ND |  | JP1M | +3V3 | Digikey | SAM1075-02-ND
LP | 1 | JP3 | Standard | CONN HEADER 2POS .100" SNGL TIN,Digikey SAM1075-02-ND |  | JP1M | GND | Digikey | SAM1075-02-ND
LP | 1 | JP4.1 | Standard | CONN HEADER 2POS .100" SNGL TIN,Digikey SAM1075-02-ND |  | JP1M | SBWTCK | Digikey | SAM1075-02-ND
LP | 1 | JP4.2 | Standard | CONN HEADER 2POS .100" SNGL TIN,Digikey SAM1075-02-ND |  | JP1M | SBWTDIO | Digikey | SAM1075-02-ND
LP | 0 | JP4.3 | Standard | CONN HEADER 2POS .100" SNGL TIN,Digikey SAM1075-02-ND |  | JP1M | SBWDAT (dnp) | Digikey | SAM1075-02-ND
LP | 1 | JP6.1 | Standard | CONN HEADER 2POS .100" SNGL TIN,Digikey SAM1075-02-ND |  | JP1M | TXD | Digikey | SAM1075-02-ND
LP | 1 | JP6.2 | Standard | CONN HEADER 2POS .100" SNGL TIN,Digikey SAM1075-02-ND |  | JP1M | RXD | Digikey | SAM1075-02-ND
LP | 1 | JP6.3 | Standard | CONN HEADER 2POS .100" SNGL TIN,Digikey SAM1075-02-ND |  | JP1M | CTS | Digikey | SAM1075-02-ND
LP | 1 | JP6.4 | Standard | CONN HEADER 2POS .100" SNGL TIN,Digikey SAM1075-02-ND |  | JP1M | RTS | Digikey | SAM1075-02-ND
LP | 1 | JP8 | Standard | CONN HEADER 2POS .100" SNGL TIN,Digikey SAM1075-02-ND |  | JP1 | LED1_PWR | Digikey | SAM1075-02-ND
Hub | 1 | L401 | Taiyo Yuden | INDUCTOR 2.2UH 20% SMD,Digikey 587-1638-1-ND | NR3010T2R2M | L-NR3010 | 2.2uH (NR3010T2R2M) | Digikey | 587-1638-1-ND
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

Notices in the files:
docs/MSP-EXP430F5529LP_Hardware_Design_Files/Hardware/MSP-EXP430F5529LP.brd:
(C)2003 A. DANNENBERG
parts and their libraries:
TI-LaunchPad-Eagle: As far as I know the LaunchPad rocket is released by TI under the Creative Commons license.
